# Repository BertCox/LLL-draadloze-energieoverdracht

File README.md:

# LLL-draadloze-energieoverdracht
PCB ontwerpen van de transmitter en receiver voor Levenslang Leren binnen de KU Leuven, campus Rabot.

De zender bestaat uit één enkele PCB, de ontvanger uit 4 aparte PCB's die met elkaar dienen te worden verbonden.
Een overzicht van de nodige componenten per PCB kan terug gevonden worden in de BOM-files (Bill of Material)

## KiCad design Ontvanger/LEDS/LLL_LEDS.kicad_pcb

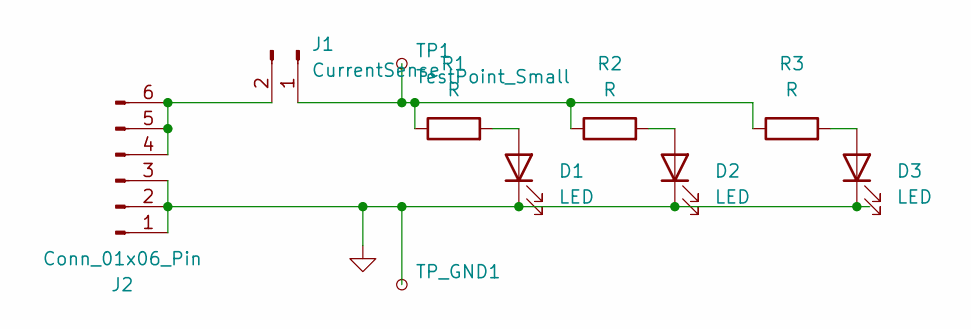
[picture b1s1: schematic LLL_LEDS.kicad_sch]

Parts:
D1, D2, D3: LED; LED_0805_2012Metric_Pad1.15x1.40mm_HandSolder
J1: CurrentSense; PinHeader_1x02_P2.54mm_Vertical
J2: Conn_01x06_Pin; Connector_Male_LLL
R1, R2, R3: R; R_0805_2012Metric_Pad1.20x1.40mm_HandSolder
TP1: TestPoint_Small; TestPoint_Loop_D1.80mm_Drill1.0mm_Beaded
TP_GND1: TestPoint_Small; TestPoint_Loop_D2.50mm_Drill1.0mm

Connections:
GND: D1.1 (K), D2.1 (K), D3.1 (K), J2.1, J2.2, J2.3, TP_GND1.1
unnamed: D1.2 (A), R1.2
unnamed: D2.2 (A), R2.2
unnamed: D3.2 (A), R3.2
unnamed: J1.1, R1.1, R2.1, R3.1, TP1.1
unnamed: J1.2, J2.4, J2.5, J2.6

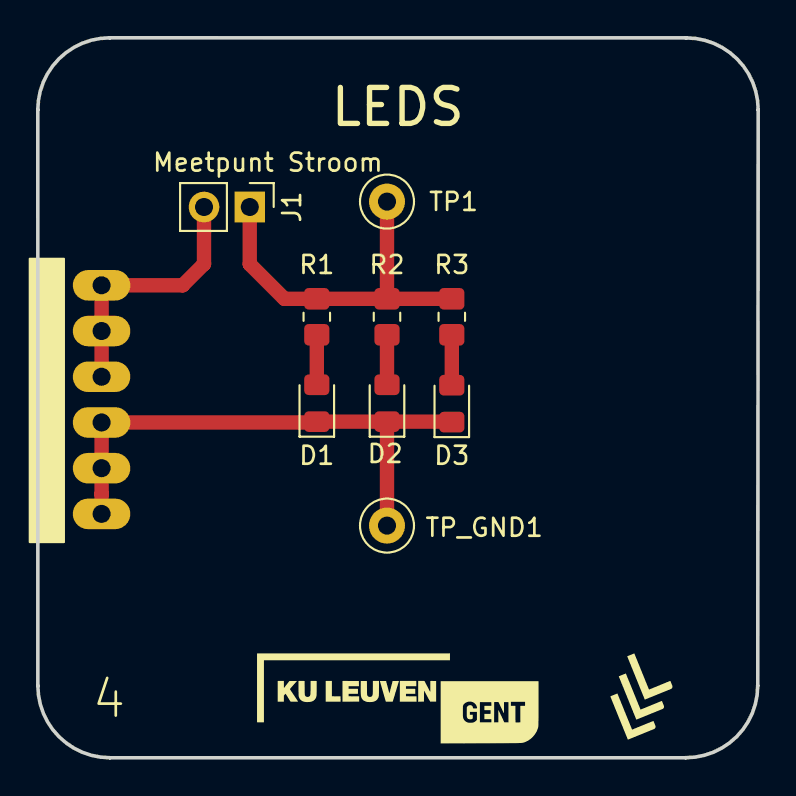
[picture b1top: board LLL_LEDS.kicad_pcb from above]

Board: 2 copper layers, 40.0 x 40.0 mm, 10 parts (0 on the bottom side), 6 nets.

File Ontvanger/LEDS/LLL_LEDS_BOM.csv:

"Id";"Designator";"Footprint";"Quantity";"Designation";"Supplier and ref";
1;"D1,D2,D3";"LED_0805_2012Metric_Pad1.15x1.40mm_HandSolder";3;"LED";;;
2;"R3,R2,R1";"R_0805_2012Metric_Pad1.20x1.40mm_HandSolder";3;"R";;;
3;"TP1";"TestPoint_Loop_D1.80mm_Drill1.0mm_Beaded";1;"TestPoint_Small";;;
4;"J1";"PinHeader_1x02_P2.54mm_Vertical";1;"CurrentSense";;;
5;"TP_GND1";"TestPoint_Loop_D2.50mm_Drill1.0mm";1;"TestPoint_Small";;;
6;"J2";"Connector_Male_LLL";1;"Conn_01x06_Pin";;;

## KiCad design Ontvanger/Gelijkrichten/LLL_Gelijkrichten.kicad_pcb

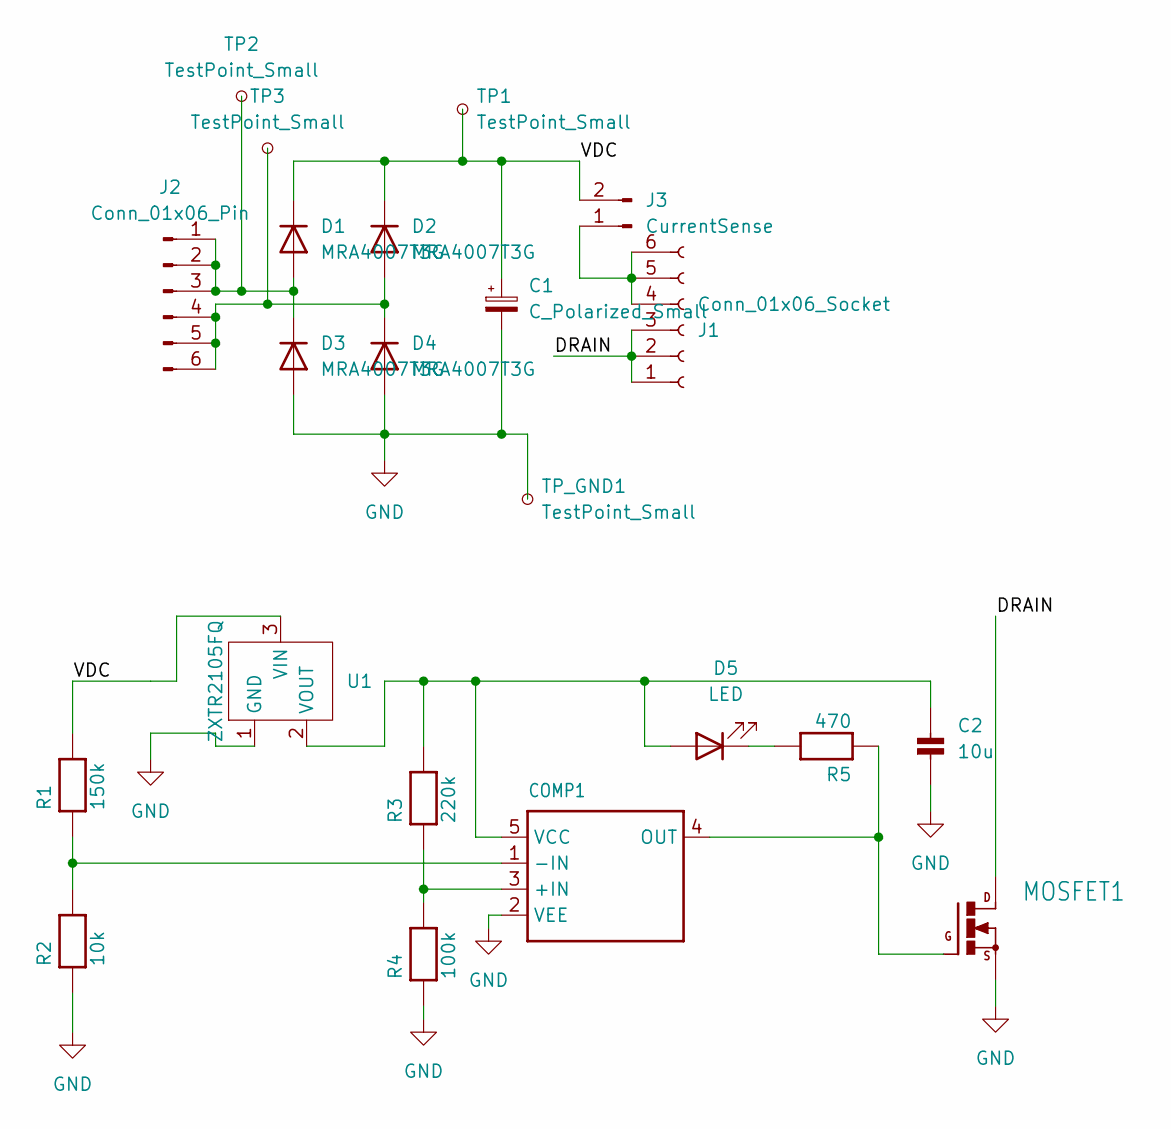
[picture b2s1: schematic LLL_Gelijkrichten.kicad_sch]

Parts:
C1: C_Polarized_Small; CP_Elec_6.3x5.9
C2: 10u; C_0805_2012Metric_Pad1.18x1.45mm_HandSolder
COMP1: BA8391G-TR; SOT95P280X125-5N
D1, D2, D3, D4: MRA4007T3G; D_SMA
D5: LED; LED_0805_2012Metric_Pad1.15x1.40mm_HandSolder
J1: Conn_01x06_Socket; Connector_Female_LLL
J2: Conn_01x06_Pin; Connector_Male_LLL
J3: CurrentSense; PinHeader_1x02_P2.54mm_Vertical
MOSFET1: N-MOSFET-SO8S; SOIC127P600X175-8N
R1: 150k; R_0805_2012Metric_Pad1.20x1.40mm_HandSolder
R2: 10k; R_0805_2012Metric_Pad1.20x1.40mm_HandSolder
R3: 220k; R_0805_2012Metric_Pad1.20x1.40mm_HandSolder
R4: 100k; R_0805_2012Metric_Pad1.20x1.40mm_HandSolder
R5: 470; R_0805_2012Metric_Pad1.20x1.40mm_HandSolder
TP1, TP2, TP3: TestPoint_Small; TestPoint_Loop_D1.80mm_Drill1.0mm_Beaded
TP_GND1: TestPoint_Small; TestPoint_Loop_D2.50mm_Drill1.0mm
U1: ZXTR2105FQ; SOT91P240X110-3N

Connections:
/DRAIN: J1.1, J1.2, J1.3, MOSFET1.5 (D), MOSFET1.6 (D), MOSFET1.7 (D), MOSFET1.8 (D)
/VDC: C1.1, D1.1 (K), D2.1 (K), J3.2, R1.2, TP1.1, U1.3 (VIN)
GND: C1.2, C2.2, COMP1.2 (VEE), D3.2 (A), D4.2 (A), MOSFET1.1 (S), MOSFET1.2 (S), MOSFET1.3 (S), R2.1, R4.1, U1.1 (GND); also elsewhere on the board
unnamed: C2.1, COMP1.5 (VCC), D5.2 (A), R3.2, U1.2 (VOUT)
unnamed: COMP1.3 (+IN), R3.1, R4.2
unnamed: COMP1.1 (-IN), R1.1, R2.2
unnamed: COMP1.4 (OUT), MOSFET1.4 (G), R5.1
unnamed: D1.2 (A), D3.1 (K), J2.1, J2.2, J2.3, TP2.1
unnamed: D2.2 (A), D4.1 (K), J2.4, J2.5, J2.6, TP3.1
unnamed: D5.1 (K), R5.2
unnamed: J1.4, J1.5, J1.6, J3.1

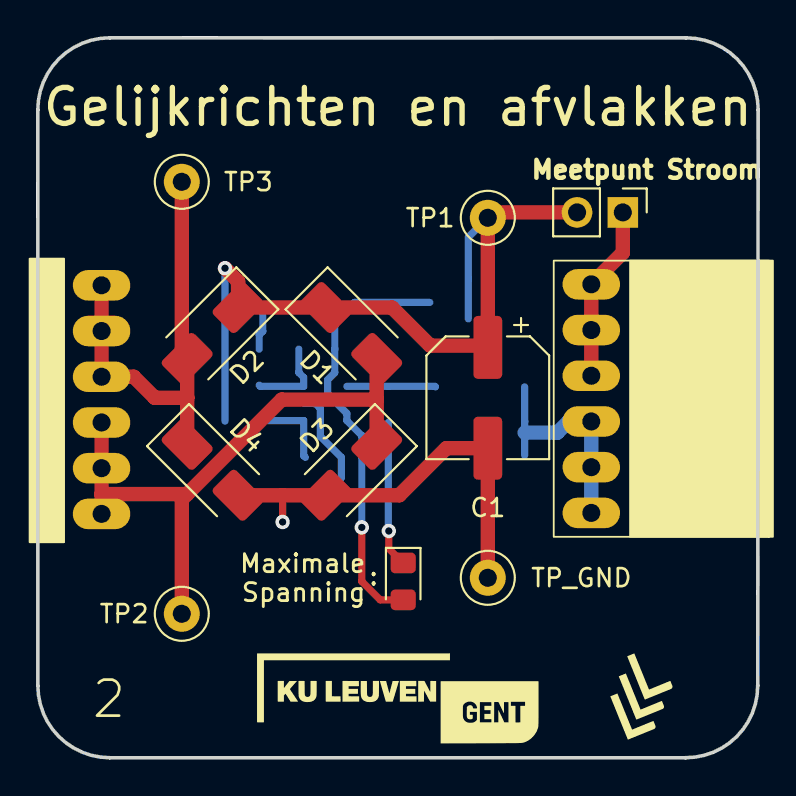
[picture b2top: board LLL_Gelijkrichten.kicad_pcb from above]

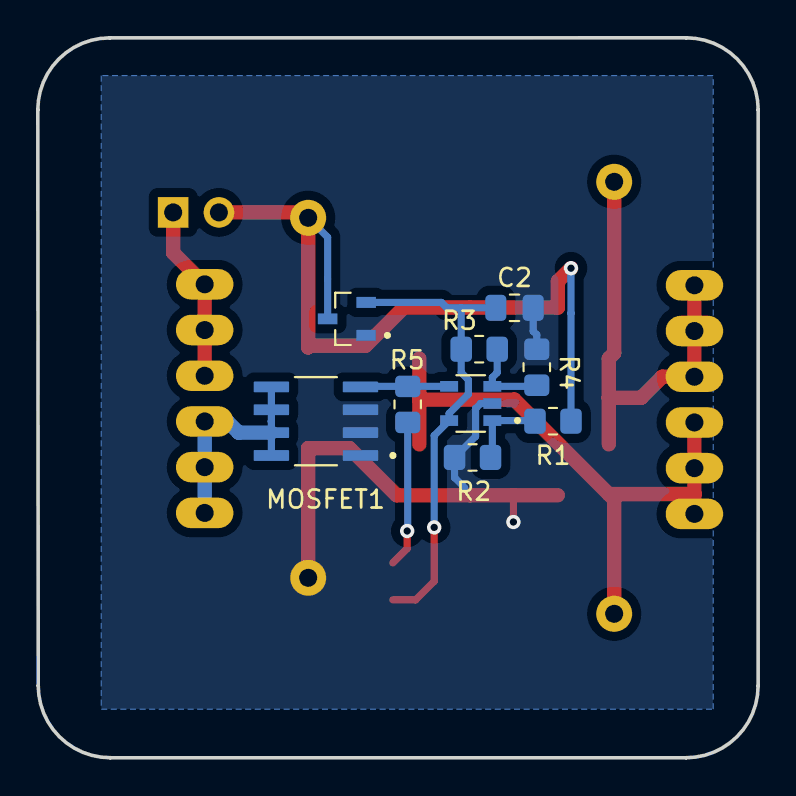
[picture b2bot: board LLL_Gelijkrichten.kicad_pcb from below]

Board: 2 copper layers, 40.0 x 40.0 mm, 22 parts (9 on the bottom side), 11 nets.

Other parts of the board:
TP_GND: TestPoint_Small; TestPoint_Loop_D2.50mm_Drill1.0mm

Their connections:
GND: TP_GND.1; also elsewhere on the board

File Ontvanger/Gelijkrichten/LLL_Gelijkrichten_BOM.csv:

"Id";"Designator";"Footprint";"Quantity";"Designation";"Supplier and ref";
1;"D4,D1,D2,D3";"D_SMA";4;"MRA4007T3G";;;
2;"TP1,TP2,TP3";"TestPoint_Loop_D1.80mm_Drill1.0mm_Beaded";3;"TestPoint_Small";;;
3;"J3";"PinHeader_1x02_P2.54mm_Vertical";1;"CurrentSense";;;
4;"J1";"Connector_Female_LLL";1;"Conn_01x06_Socket";;;
5;"D5";"LED_0805_2012Metric_Pad1.15x1.40mm_HandSolder";1;"LED";;;
6;"C1";"CP_Elec_6.3x5.9";1;"C_Polarized_Small";;;
7;"J2";"Connector_Male_LLL";1;"Conn_01x06_Pin";;;
8;"TP_GND";"TestPoint_Loop_D2.50mm_Drill1.0mm";1;"TestPoint_Small";;;
9;"R3,R2,R1,R4";"R_0805_2012Metric_Pad1.20x1.40mm_HandSolder";4;"RESISTOR0603";;;
10;"COMP1";"SOT95P280X125-5N";1;"BA8391G-TR";;;
11;"C2";"C_0805_2012Metric_Pad1.18x1.45mm_HandSolder";1;"10u";;;
12;"U1";"SOT91P240X110-3N";1;"ZXTR2105FQ";;;
13;"R5";"R_0805_2012Metric_Pad1.20x1.40mm_HandSolder";1;"470";;;
14;"MOSFET1";"SOIC127P600X175-8N";1;"N-MOSFET-SO8S";;;

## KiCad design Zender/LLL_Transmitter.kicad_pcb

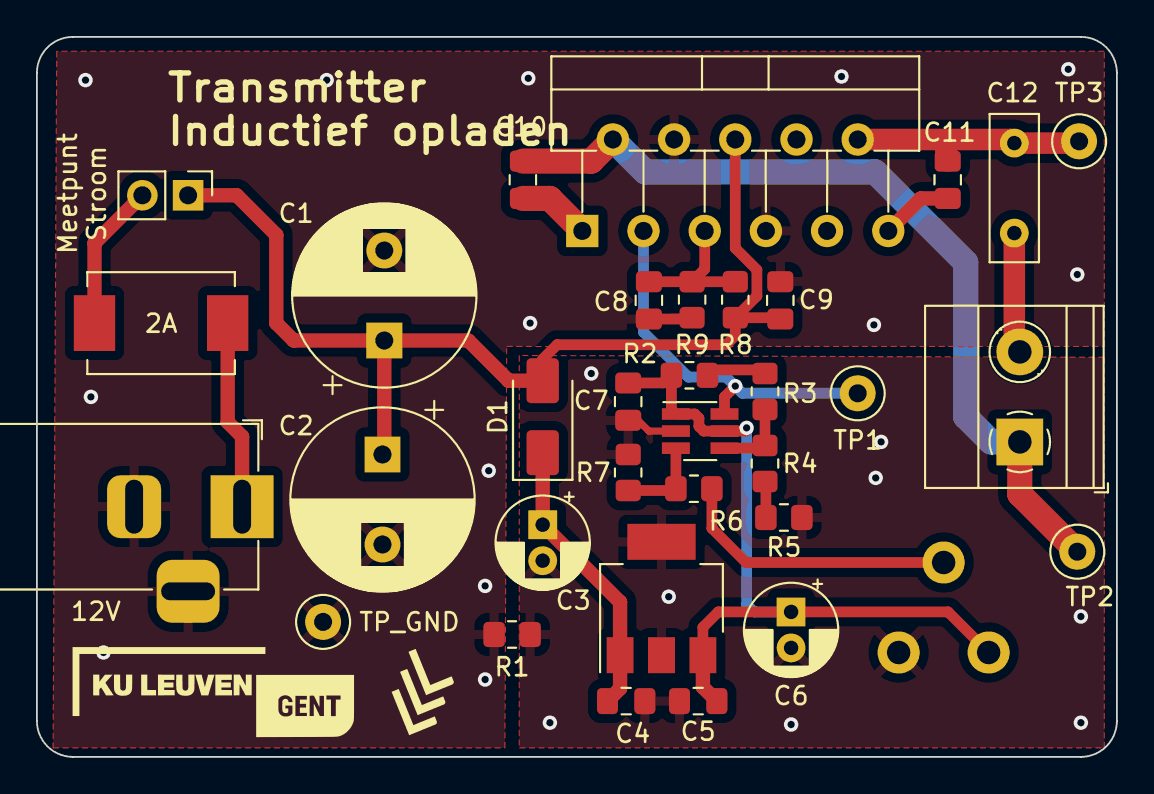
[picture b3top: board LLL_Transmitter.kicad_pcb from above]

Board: 2 copper layers, 60.0 x 40.0 mm, 34 parts (0 on the bottom side), 19 nets.

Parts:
C1, C2: 1200u; CP_Radial_D10.0mm_P5.00mm
C3, C6: 100u; CP_Radial_D5.0mm_P2.00mm
C4, C5, C7, C8, C9: 100n; C_0805_2012Metric_Pad1.18x1.45mm_HandSolder
C10, C11: 10n; C_0805_2012Metric_Pad1.18x1.45mm_HandSolder
C12: 390n; C_Disc_D8.0mm_W2.5mm_P5.00mm
D1: 1N4004; D_SMA
F1: Fuse; Fuse_Bourns_MF-SM_7.98x5.44mm
IC1: LM18201; TO-220-11_P3.4x5.08mm_StaggerOdd_Lead4.85mm_Vertical
J1: DCJ0303; BarrelJack_Horizontal
J2: CurrentSense; PinHeader_1x02_P2.54mm_Vertical
J3: Screw_Terminal_01x02; TerminalBlock_Phoenix_MKDS-1,5-2_1x02_P5.00mm_Horizontal
R1: 0; R_0805_2012Metric_Pad1.20x1.40mm_HandSolder
R2: 68k; R_0805_2012Metric_Pad1.20x1.40mm_HandSolder
R3: 910k; R_0805_2012Metric_Pad1.20x1.40mm_HandSolder
R4, R6, R7, R8, R9: 100k; R_0805_2012Metric_Pad1.20x1.40mm_HandSolder
R5: 2k; R_0805_2012Metric_Pad1.20x1.40mm_HandSolder
RV1: 1k; Potentiometer_Piher_PT-10-V05_Vertical
TP1, TP2, TP3: TestPoint_Small; TestPoint_Loop_D1.80mm_Drill1.0mm_Beaded
TP_GND: TestPoint_Small; TestPoint_Loop_D2.50mm_Drill1.0mm
U1: LM2936-5.0; SOT-223-3_TabPin2
U2: LTC6990CS6TRPBF; SOT-23-6_Handsoldering

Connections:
+12V: C1.1, C2.1, C9.1, D1.2 (A), IC1.6 (VS), J2.1, R8.2
AGND: C1.2, C2.2, C8.2, C9.2, IC1.4 (BREAK), IC1.7 (GND), J1.2, J1.3, R1.1, R9.1, TP_GND.1
GND: C3.2, C4.2, C5.2, C6.2, C7.2, R1.2, R5.1, R7.1, RV1.3, U1.2 (GND), U2.2 (GND)
unnamed: C3.1, C4.1, D1.1 (K), U1.1 (VI)
unnamed: F1.2, J1.1
unnamed: C10.2, IC1.1 (BOOTSTRAP1)
unnamed: C11.1, IC1.11 (BOOTSTRAP2)
unnamed: IC1.3 (DIRECTION), TP1.1, U2.6 (OUT)
unnamed: C10.1, IC1.2 (OUTPUT1), J3.1, TP2.1
unnamed: C11.2, C12.1, IC1.10 (OUTPUT2), TP3.1
unnamed: C8.1, IC1.5 (PWM), R8.1, R9.2
unnamed: F1.1, J2.2
unnamed: C12.2, J3.2
unnamed: R2.1, R3.2
unnamed: R4.1, R5.2
unnamed: R6.2, RV1.2
unnamed: C5.1, C6.1, C7.1, R2.2, RV1.1, U1.3 (VO), U2.1 (OE), U2.5 (V+)
unnamed: R3.1, R4.2, U2.4 (DIV)
unnamed: R6.1, R7.2, U2.3 (SET)

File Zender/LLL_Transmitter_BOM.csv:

"Id";"Designator";"Footprint";"Quantity";"Designation";"Supplier and ref";
1;"C12";"C_Disc_D8.0mm_W2.5mm_P5.00mm";1;"390n";;;
2;"J1";"BarrelJack_Horizontal";1;"DCJ0303";;;
3;"D1";"D_SMA";1;"1N4004";;;
4;"C2,C1";"CP_Radial_D10.0mm_P5.00mm";2;"1200u";;;
5;"R8,R4,R9,R6,R7";"R_0805_2012Metric_Pad1.20x1.40mm_HandSolder";5;"100k";;;
6;"IC1";"TO-220-11_P3.4x5.08mm_StaggerOdd_Lead4.85mm_Vertical";1;"LM18201";;;
7;"C11,C10";"C_0805_2012Metric_Pad1.18x1.45mm_HandSolder";2;"10n";;;
8;"TP1,TP3,TP2";"TestPoint_Loop_D1.80mm_Drill1.0mm_Beaded";3;"TestPoint_Small";;;
9;"RV1";"Potentiometer_Piher_PT-10-V05_Vertical";1;"1k";;;
10;"F1";"Fuse_Bourns_MF-SM_7.98x5.44mm";1;"Fuse";;;
11;"TP_GND";"TestPoint_Loop_D2.50mm_Drill1.0mm";1;"TestPoint_Small";;;
12;"J2";"PinHeader_1x02_P2.54mm_Vertical";1;"CurrentSense";;;
13;"C9,C4,C5,C8,C7";"C_0805_2012Metric_Pad1.18x1.45mm_HandSolder";5;"100n";;;
14;"R5";"R_0805_2012Metric_Pad1.20x1.40mm_HandSolder";1;"2k";;;
15;"R2";"R_0805_2012Metric_Pad1.20x1.40mm_HandSolder";1;"68k";;;
16;"J3";"TerminalBlock_Phoenix_MKDS-1,5-2_1x02_P5.00mm_Horizontal";1;"Screw_Terminal_01x02";;;
17;"U2";"SOT-23-6_Handsoldering";1;"LTC6990CS6TRPBF";;;
18;"C6,C3";"CP_Radial_D5.0mm_P2.00mm";2;"100u";;;
19;"U1";"SOT-223-3_TabPin2";1;"LM2936-5.0";;;
20;"R3";"R_0805_2012Metric_Pad1.20x1.40mm_HandSolder";1;"910k";;;
21;"R1";"R_0805_2012Metric_Pad1.20x1.40mm_HandSolder";1;"0";;;

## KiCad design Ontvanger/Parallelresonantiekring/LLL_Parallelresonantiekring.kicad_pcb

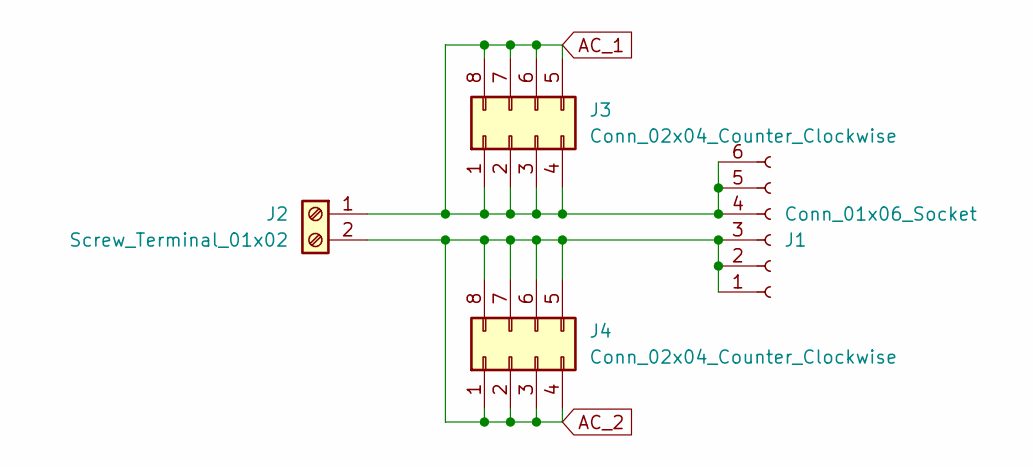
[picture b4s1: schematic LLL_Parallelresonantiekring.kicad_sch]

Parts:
J1: Conn_01x06_Socket; Connector_Female_LLL
J2: Screw_Terminal_01x02; TerminalBlock_RND_205-00001_1x02_P5.00mm_Horizontal
J3, J4: Conn_02x04_Counter_Clockwise; conn_2x04_LLL

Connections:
AC_1: J1.4, J1.5, J1.6, J2.1, J3.1, J3.2, J3.3, J3.4, J3.5, J3.6, J3.7, J3.8
AC_2: J1.1, J1.2, J1.3, J2.2, J4.1, J4.2, J4.3, J4.4, J4.5, J4.6, J4.7, J4.8

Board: 2 copper layers, 4 parts (0 on the bottom side), 2 nets, no tracks yet.

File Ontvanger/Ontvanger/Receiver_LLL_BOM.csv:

"Id";"Designator";"Footprint";"Quantity";"Designation";"Supplier and ref";
1;"J2";"TerminalBlock_RND_205-00001_1x02_P5.00mm_Horizontal";1;"Screw_Terminal_01x02";;;
2;"J1";"Connector_Female_LLL";1;"Conn_01x06_Socket";;;
3;"J3,J4";"conn_2x04_LLL";2;"Conn_02x04_Counter_Clockwise";;;

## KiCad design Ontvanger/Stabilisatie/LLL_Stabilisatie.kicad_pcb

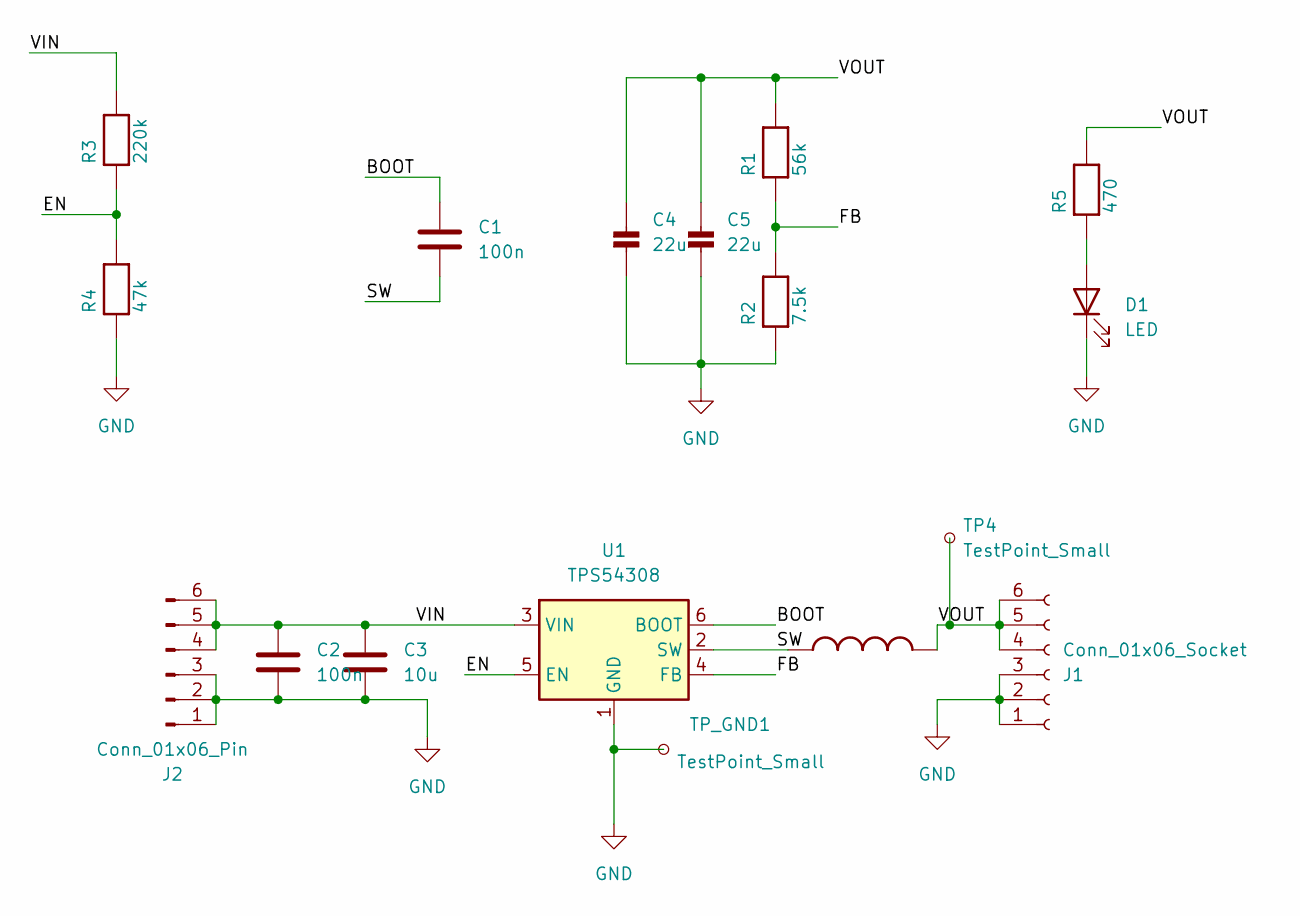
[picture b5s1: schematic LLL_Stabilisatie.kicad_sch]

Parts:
C1, C2: 100n; C_0805_2012Metric_Pad1.18x1.45mm_HandSolder
C3: 10u; C_0805_2012Metric_Pad1.18x1.45mm_HandSolder
C4, C5: 22u; C_0805_2012Metric_Pad1.18x1.45mm_HandSolder
D1: LED; LED_0805_2012Metric_Pad1.15x1.40mm_HandSolder
J1: Conn_01x06_Socket; Connector_Female_LLL
J2: Conn_01x06_Pin; Connector_Male_LLL
L1: 10uH; L_6.3x6.3_H3
R1: 56k; R_0805_2012Metric_Pad1.20x1.40mm_HandSolder
R2: 7.5k; R_0805_2012Metric_Pad1.20x1.40mm_HandSolder
R3: 220k; R_0805_2012Metric_Pad1.20x1.40mm_HandSolder
R4: 47k; R_0805_2012Metric_Pad1.20x1.40mm_HandSolder
R5: 470; R_0805_2012Metric_Pad1.20x1.40mm_HandSolder
TP4: TestPoint_Small; TestPoint_Loop_D1.80mm_Drill1.0mm_Beaded
TP_GND1: TestPoint_Small; TestPoint_Loop_D2.50mm_Drill1.0mm
U1: TPS54308; SOT-23-6

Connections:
/BOOT: C1.1, U1.6 (BOOT)
/EN: R3.1, R4.2, U1.5 (EN)
/FB: R1.1, R2.2, U1.4 (FB)
/SW: C1.2, L1.1, U1.2 (SW)
/VIN: C2.1, C3.1, J2.4, J2.5, J2.6, R3.2, U1.3 (VIN)
/VOUT: C4.1, C5.1, J1.4, J1.5, J1.6, L1.2, R1.2, R5.2, TP4.1
GND: C2.2, C3.2, C4.2, C5.2, D1.1 (K), J1.1, J1.2, J1.3, J2.1, J2.2, J2.3, R2.1, R4.1, TP_GND1.1, U1.1 (GND); also elsewhere on the board
unnamed: D1.2 (A), R5.1

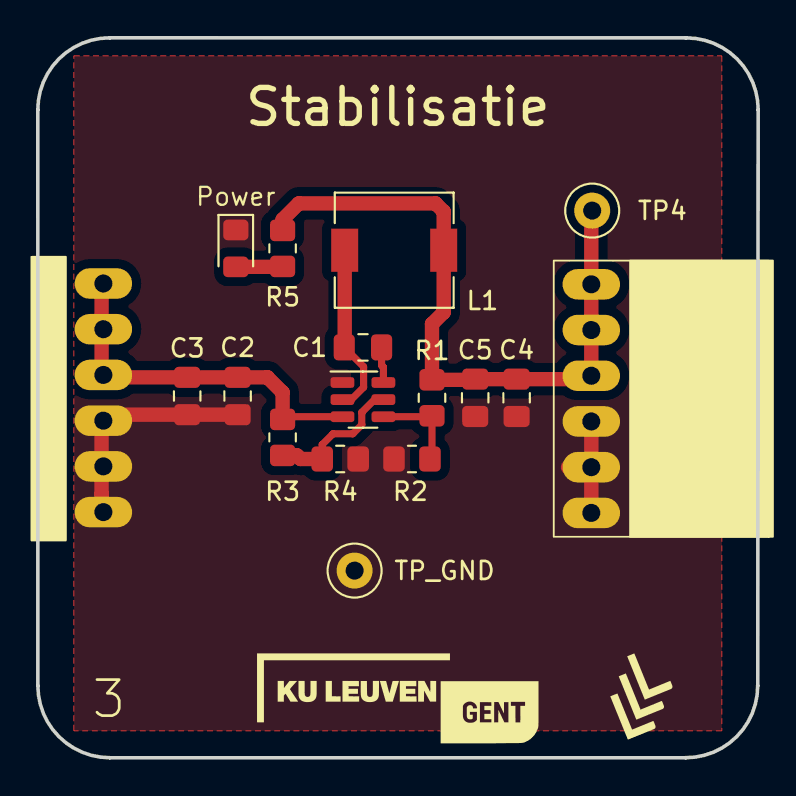
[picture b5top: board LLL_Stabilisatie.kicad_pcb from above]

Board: 2 copper layers, 40.0 x 40.0 mm, 17 parts (0 on the bottom side), 8 nets.

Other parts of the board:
TP_GND: TestPoint_Small; TestPoint_Loop_D2.50mm_Drill1.0mm

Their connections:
GND: TP_GND.1; also elsewhere on the board

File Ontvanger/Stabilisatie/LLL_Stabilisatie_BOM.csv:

"Id";"Designator";"Footprint";"Quantity";"Designation";"Supplier and ref";
1;"R3";"R_0805_2012Metric_Pad1.20x1.40mm_HandSolder";1;"220k";;;
2;"TP4";"TestPoint_Loop_D1.80mm_Drill1.0mm_Beaded";1;"TestPoint_Small";;;
3;"D1";"LED_0805_2012Metric_Pad1.15x1.40mm_HandSolder";1;"LED";;;
4;"J1";"Connector_Female_LLL";1;"Conn_01x06_Socket";;;
5;"L1";"L_6.3x6.3_H3";1;"10uH";;;
6;"R4";"R_0805_2012Metric_Pad1.20x1.40mm_HandSolder";1;"47k";;;
7;"C4,C5";"C_0805_2012Metric_Pad1.18x1.45mm_HandSolder";2;"22u";;;
8;"C1,C2";"C_0805_2012Metric_Pad1.18x1.45mm_HandSolder";2;"100n";;;
9;"U1";"SOT-23-6";1;"TPS54308";;;
10;"R1,R5";"R_0805_2012Metric_Pad1.20x1.40mm_HandSolder";2;"56k";;;
11;"R2";"R_0805_2012Metric_Pad1.20x1.40mm_HandSolder";1;"7.5k";;;
12;"J2";"Connector_Male_LLL";1;"Conn_01x06_Pin";;;
13;"C3";"C_0805_2012Metric_Pad1.18x1.45mm_HandSolder";1;"10u";;;
14;"TP_GND";"TestPoint_Loop_D2.50mm_Drill1.0mm";1;"TestPoint_Small";;;

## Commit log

2024-11-15 Herorganisatie
2024-11-15 Added BOM files
